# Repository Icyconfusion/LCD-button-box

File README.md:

# LCD-button-box
A DIY stream deck style button box using a 3.5" LCD, tact switches and an ESP32 Devkit V1.

The button box uses an LCD seated at the bottom of the case. Above that, a PCB is suspended, containing the necessary tact switches. The PCB has square cutout holes to show the LCD image through. To press the buttons, there is a 3d printed stand on each set of 4 switches (one button), holding a clear acrylic square. Through this mechanism, the LCD is visible, and pressing the acylic presses the tact switches, registering a keypress. The bottom right button functions as a change layer button, where pressing that will cycle the button box to a new 'layer', with different icons and key outputs. 

The case is made using two parts, a base and a top. The base has 4 'legs' inside it to hold the lcd. 
 
Above that, there is a perimeter ledge for the PCB to sit on. 

The top attaches to the base using 4xM3 heatset inserts. 

The ESP32 and switches are soldered to the PCB, and headers are soldered in place of the LCD. Jumper wires connect these headers down, underneath the LCD and into the pins on the bottom of the LCD.

The button box connects to devices by bluetooth, but requires a micro usb power source. The button box outputs macros using a combination of CTRL, SHIFT, ALT and F14+ keys to ensure unique macros.

Bill of materials
1x ESP32 Devkit V1

24x Tactile switch 6x6x5mm

1x 3.5" TFT 480x320 LCD screen

1x 40 pin male headers

20x Female - female jumper wires

3d printed parts

Acrylic sheet

PCB

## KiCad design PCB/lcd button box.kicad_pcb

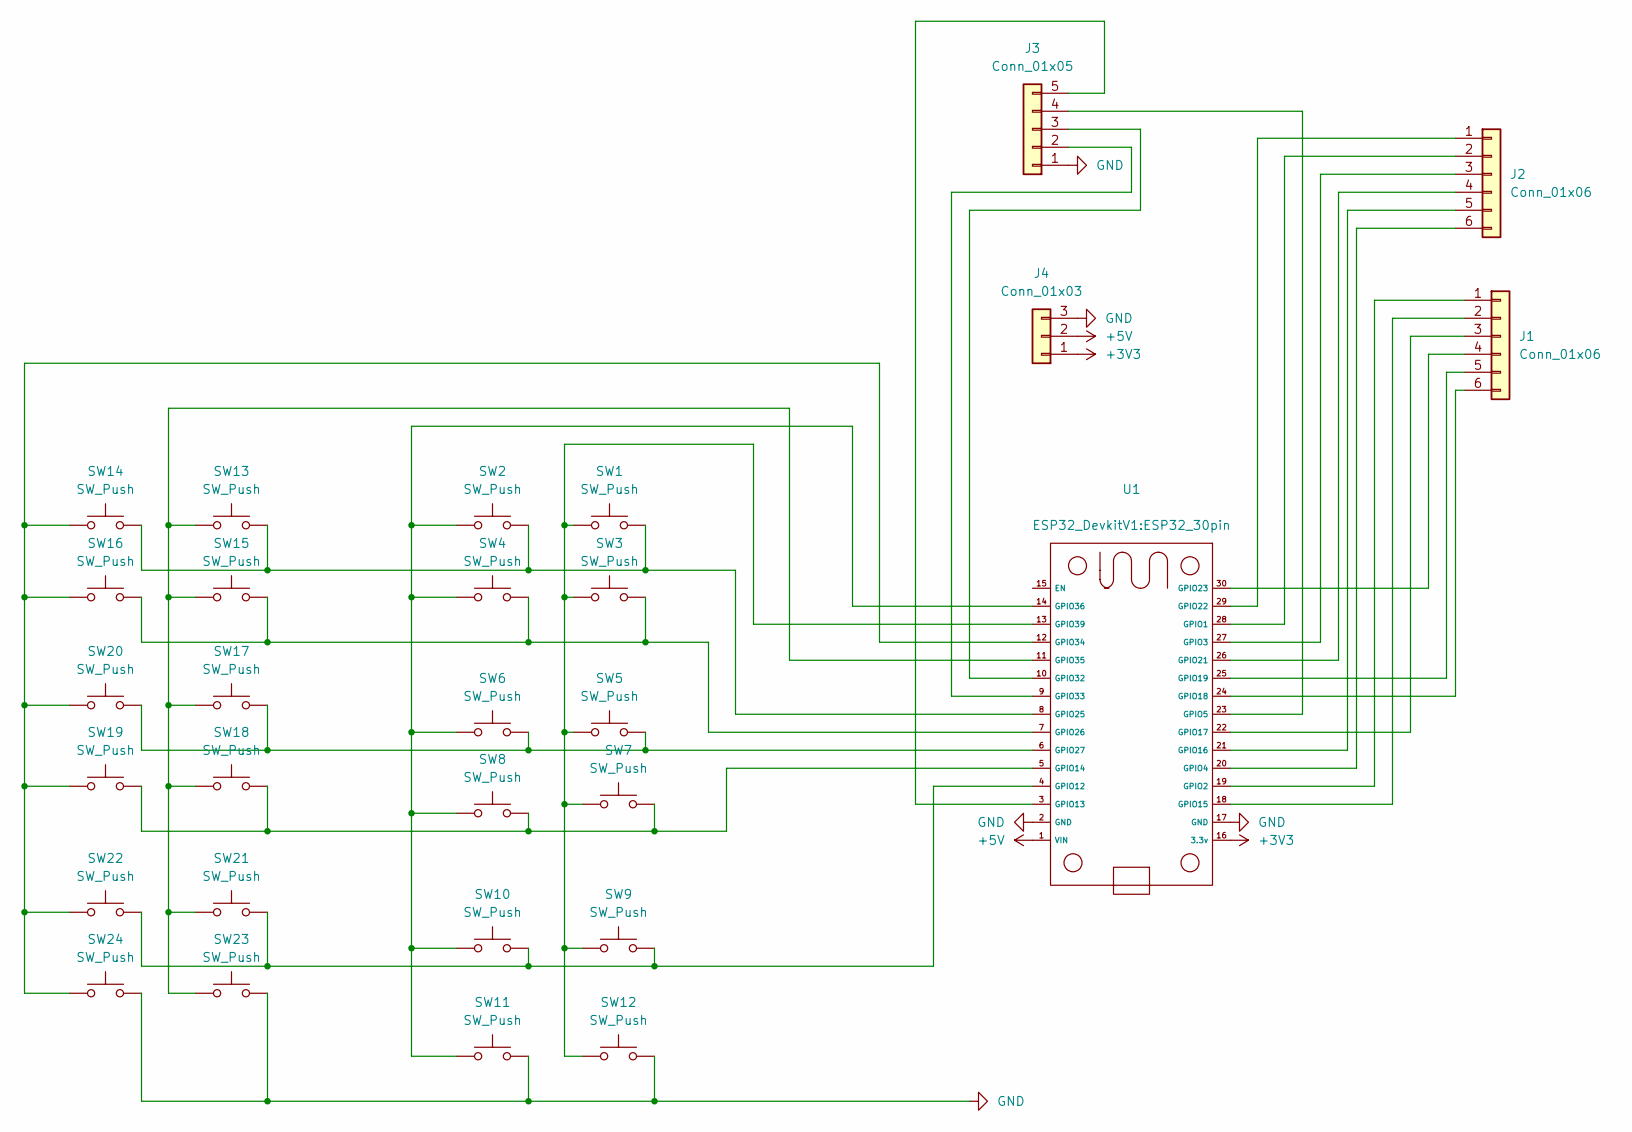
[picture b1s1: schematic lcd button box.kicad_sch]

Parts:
J1, J2: Conn_01x06; PinHeader_1x06_P2.54mm_Vertical
J3: Conn_01x05; PinHeader_1x05_P2.54mm_Vertical
J4: Conn_01x03; PinHeader_1x03_P2.54mm_Vertical
SW1, SW2, SW3, SW4, SW5, SW6, SW7, SW8, SW9, SW10, SW11, SW12, SW13, SW14, SW15, SW16, SW17, SW18, SW19, SW20, SW21, SW22, SW23, SW24: SW_Push; SW_PUSH_6mm
U1: ESP32_30pin

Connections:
+3V3: J4.1, U1.16 (3.3v)
+5V: J4.2, U1.1 (VIN)
GND: J3.1, J4.3, SW11.2, SW12.2, SW23.2, SW24.2, U1.2 (GND), U1.17 (GND)
unnamed: J1.1, U1.19 (GPIO2)
unnamed: J1.2, U1.18 (GPIO15)
unnamed: J1.3, U1.22 (GPIO17)
unnamed: J1.4, U1.30 (GPIO23)
unnamed: J1.5, U1.25 (GPIO19)
unnamed: J1.6, U1.24 (GPIO18)
unnamed: J2.1, U1.29 (GPIO22)
unnamed: J2.2, U1.28 (GPIO1)
unnamed: J2.3, U1.27 (GPIO3)
unnamed: J2.4, U1.26 (GPIO21)
unnamed: J2.5, U1.21 (GPIO16)
unnamed: J2.6, U1.20 (GPIO4)
unnamed: J3.2, U1.9 (GPIO33)
unnamed: J3.3, U1.10 (GPIO32)
unnamed: J3.4, U1.23 (GPIO5)
unnamed: J3.5, U1.3 (GPIO13)
unnamed: SW9.2, SW10.2, SW21.2, SW22.2, U1.4 (GPIO12)
unnamed: SW7.2, SW8.2, SW18.2, SW19.2, U1.5 (GPIO14)
unnamed: SW1.2, SW2.2, SW13.2, SW14.2, U1.8 (GPIO25)
unnamed: SW3.2, SW4.2, SW15.2, SW16.2, U1.7 (GPIO26)
unnamed: SW5.2, SW6.2, SW17.2, SW20.2, U1.6 (GPIO27)
unnamed: SW14.1, SW16.1, SW19.1, SW20.1, SW22.1, SW24.1, U1.12 (GPIO34)
unnamed: SW13.1, SW15.1, SW17.1, SW18.1, SW21.1, SW23.1, U1.11 (GPIO35)
unnamed: SW2.1, SW4.1, SW6.1, SW8.1, SW10.1, SW11.1, U1.14 (GPIO36)
unnamed: SW1.1, SW3.1, SW5.1, SW7.1, SW9.1, SW12.1, U1.13 (GPIO39)

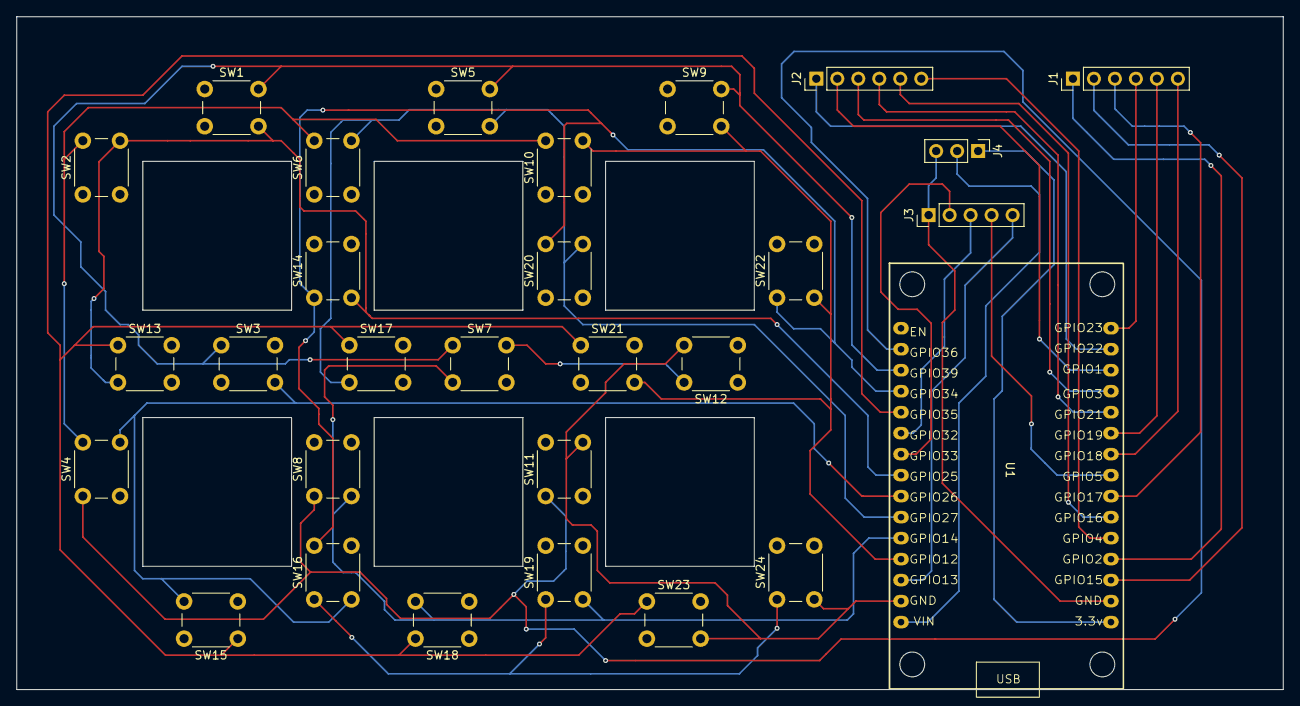
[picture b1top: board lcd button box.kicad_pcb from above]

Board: 2 copper layers, 153.2 x 81.4 mm, 29 parts (0 on the bottom side), 28 nets.

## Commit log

2025-12-14 Added CAD files
2025-12-15 Added necessary files
2025-12-16 Added BOM
